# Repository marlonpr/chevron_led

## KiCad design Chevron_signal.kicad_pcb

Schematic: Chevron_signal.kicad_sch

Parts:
D1, D2, D3, D4, D5, D6, D7, D8, D9, D10, D11, D12, D13, D14, D15, D16, D17, D18, D19, D20, D21, D22, D23, D24, D25, D26, D27, D28, D29, D30, D31, D32, D33, D34, D35, D36, D37, D38, D39, D40, D41, D42, D43, D44, D45, D46, D47, D48, D49, D50, D51, D52, D53, D54, D55, D56, D57, D58, D59, D60, D61, D62, D63, D64, D65, D66, D67, D68, D69, D70, D71, D72, D73, D74, D75, D76, D77, D78, D79, D80, D81, D82, D83, D84, D85, D86, D87, D88, D89, D90, D91, D92, D93, D94, D95, D96, D97, D98, D99, D100, D101, D102, D103, D104, D105, D106, D107, D108, D109, D110, D111, D112, D113, D114, D115, D116, D117, D118, D119, D120, D121, D122, D123, D124, D125, D126, D127, D128, D129, D130, D131, D132, D133, D134, D135, D136, D137, D138, D139, D140, D141, D142, D143, D144: LED_CV28
P1: 282837-2; TE_282837-2; PARTREV G3
R1, R2, R3, R4, R5, R6, R7, R8, R9, R10, R11, R12, R13, R14, R15, R16, R17, R18, R19, R20, R21, R22, R23, R24, R25, R26, R27, R28, R29, R30, R31, R32, R33, R34, R35, R36, R37, R38, R39, R40, R41, R42, R43, R44, R45, R46, R47, R48, R49, R50, R51, R52, R53, R54, R55, R56, R57, R58, R59, R60, R61, R62, R63, R64, R65, R66, R67, R68, R69, R70, R71, R72, R73, R74, R75, R76, R77, R78, R79, R80, R81, R82, R83, R84, R85, R86, R87, R88, R89, R90, R91, R92, R93, R94, R95, R96, R97, R98, R99, R100, R101, R102, R103, R104, R105, R106, R107, R108, R109, R110, R111, R112, R113, R114, R115, R116, R117, R118, R119, R120: R_Small; R_Axial_DIN0207_L6.3mm_D2.5mm_P10.16mm_Horizontal

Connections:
+12V: P1.2, R1.2, R2.2, R3.2, R4.2, R5.2, R6.2, R7.2, R8.2, R9.2, R10.2, R11.2, R12.2, R13.2, R14.2, R15.2, R16.2, R17.2, R18.2, R19.2, R20.2, R21.2, R22.2, R23.2, R24.2, R25.2, R26.2, R27.2, R28.2, R29.2, R30.2, R31.2, R32.2, R33.2, R34.2, R35.2, R36.2, R37.2, R38.2, R39.2, R40.2, R41.2, R42.2, R43.2, R44.2, R45.2, R46.2, R47.2, R48.2, R49.2, R50.2, R51.2, R52.2, R53.2, R54.2, R55.2, R56.2, R57.2, R58.2, R59.2, R60.2, R61.2, R62.2, R63.2, R64.2, R65.2, R66.2, R67.2, R68.2, R69.2, R70.2, R71.2, R72.2, R73.2, R74.2, R75.2, R76.2, R77.2, R78.2, R79.2, R80.2, R81.2, R82.2, R83.2, R84.2, R85.2, R86.2, R87.2, R88.2, R89.2, R90.2, R91.2, R92.2, R93.2, R94.2, R95.2, R96.2, R97.2, R98.2, R99.2, R100.2, R101.2, R102.2, R103.2, R104.2, R105.2, R106.2, R107.2, R108.2, R109.2, R110.2, R111.2, R112.2, R113.2, R114.2, R115.2, R116.2, R117.2, R118.2, R119.2, R120.2
GND: D1.C1, D1.C2, D1.C3, D4.C3, D5.C1, D5.C2, D7.C3, D9.C1, D9.C2, D10.C3, D13.C1, D13.C2, D13.C3, D16.C3, D17.C1, D17.C2, D19.C3, D21.C1, D21.C2, D22.C3, D25.C1, D25.C2, D25.C3, D28.C3, D29.C1, D29.C2, D31.C3, D33.C1, D33.C2, D34.C3, D37.C1, D37.C2, D37.C3, D40.C3, D41.C1, D41.C2, D43.C3, D45.C1, D45.C2, D46.C3, D49.C1, D49.C2, D49.C3, D52.C3, D53.C1, D53.C2, D55.C3, D57.C1, D57.C2, D58.C3, D61.C1, D61.C2, D61.C3, D64.C3, D65.C1, D65.C2, D67.C3, D69.C1, D69.C2, D70.C3, D73.C1, D73.C2, D73.C3, D76.C3, D77.C1, D77.C2, D79.C3, D81.C1, D81.C2, D82.C3, D85.C1, D85.C2, D85.C3, D88.C3, D89.C1, D89.C2, D91.C3, D93.C1, D93.C2, D94.C3, D97.C1, D97.C2, D97.C3, D100.C3, D101.C1, D101.C2, D103.C3, D105.C1, D105.C2, D106.C3, D109.C1, D109.C2, D109.C3, D112.C3, D113.C1, D113.C2, D115.C3, D117.C1, D117.C2, D118.C3, D121.C1, D121.C2, D121.C3, D124.C3, D125.C1, D125.C2, D127.C3, D129.C1, D129.C2, D130.C3, D133.C1, D133.C2, D133.C3, D136.C3, D137.C1, D137.C2, D139.C3, D141.C1, D141.C2, D142.C3, P1.1
unnamed: D1.A1, D2.C1
unnamed: D1.A2, D2.C2
unnamed: D1.A3, D2.C3
unnamed: D2.A1, D3.C1
unnamed: D2.A2, D3.C2
unnamed: D2.A3, D3.C3
unnamed: D3.A1, D4.C1
unnamed: D3.A2, D4.C2
unnamed: D3.A3, R1.1
unnamed: D4.A1, R2.1
unnamed: D4.A2, R3.1
unnamed: D4.A3, D5.C3
unnamed: D5.A1, D6.C1
unnamed: D5.A2, D6.C2
unnamed: D5.A3, D6.C3
unnamed: D6.A1, D7.C1
unnamed: D6.A2, D7.C2
unnamed: D6.A3, R4.1
unnamed: D7.A1, D8.C1
unnamed: D7.A2, D8.C2
unnamed: D7.A3, D8.C3
unnamed: D8.A1, R5.1
unnamed: D8.A2, R6.1
unnamed: D8.A3, D9.C3
unnamed: D9.A3, R7.1
unnamed: D10.A1, D11.C1
unnamed: D10.A2, D11.C2
unnamed: D10.A3, D11.C3
unnamed: D9.A1, D10.C1
unnamed: D9.A2, D10.C2
unnamed: D11.A1, D12.C1
unnamed: D11.A2, D12.C2
unnamed: D11.A3, D12.C3
unnamed: D12.A1, R8.1
unnamed: D12.A2, R9.1
unnamed: D12.A3, R10.1
unnamed: D13.A1, D14.C1
unnamed: D13.A2, D14.C2
unnamed: D13.A3, D14.C3
unnamed: D14.A1, D15.C1
unnamed: D14.A2, D15.C2
unnamed: D14.A3, D15.C3
unnamed: D15.A1, D16.C1
unnamed: D15.A2, D16.C2
unnamed: D15.A3, R11.1
unnamed: D16.A1, R12.1
unnamed: D16.A2, R13.1
unnamed: D16.A3, D17.C3
unnamed: D17.A1, D18.C1
unnamed: D17.A2, D18.C2
unnamed: D17.A3, D18.C3
unnamed: D18.A1, D19.C1
unnamed: D18.A2, D19.C2
unnamed: D18.A3, R14.1
unnamed: D19.A1, D20.C1
unnamed: D19.A2, D20.C2
unnamed: D19.A3, D20.C3
unnamed: D20.A1, R15.1
unnamed: D20.A2, R16.1
unnamed: D20.A3, D21.C3
unnamed: D21.A1, D22.C1
unnamed: D21.A2, D22.C2
unnamed: D21.A3, R17.1
unnamed: D22.A1, D23.C1
unnamed: D22.A2, D23.C2
unnamed: D22.A3, D23.C3
unnamed: D23.A1, D24.C1
unnamed: D23.A2, D24.C2
unnamed: D23.A3, D24.C3
unnamed: D24.A1, R18.1
unnamed: D24.A2, R19.1
unnamed: D24.A3, R20.1
unnamed: D25.A1, D26.C1
unnamed: D25.A2, D26.C2
unnamed: D25.A3, D26.C3
unnamed: D26.A1, D27.C1
unnamed: D26.A2, D27.C2
unnamed: D26.A3, D27.C3
unnamed: D27.A1, D28.C1
unnamed: D27.A2, D28.C2
unnamed: D27.A3, R21.1
unnamed: D28.A1, R22.1
unnamed: D28.A2, R23.1
unnamed: D28.A3, D29.C3
unnamed: D29.A1, D30.C1
unnamed: D29.A2, D30.C2
unnamed: D29.A3, D30.C3
unnamed: D30.A1, D31.C1
unnamed: D30.A2, D31.C2
unnamed: D30.A3, R24.1
unnamed: D31.A1, D32.C1
unnamed: D31.A2, D32.C2
unnamed: D31.A3, D32.C3
unnamed: D32.A1, R25.1
unnamed: D32.A2, R26.1
unnamed: D32.A3, D33.C3
unnamed: D33.A1, D34.C1
unnamed: D33.A2, D34.C2
unnamed: D33.A3, R27.1
unnamed: D34.A1, D35.C1
unnamed: D34.A2, D35.C2
unnamed: D34.A3, D35.C3
unnamed: D35.A1, D36.C1
unnamed: D35.A2, D36.C2
unnamed: D35.A3, D36.C3
unnamed: D36.A1, R28.1
unnamed: D36.A2, R29.1
unnamed: D36.A3, R30.1
unnamed: D37.A1, D38.C1
unnamed: D37.A2, D38.C2
unnamed: D37.A3, D38.C3
unnamed: D38.A1, D39.C1
unnamed: D38.A2, D39.C2
unnamed: D38.A3, D39.C3
unnamed: D39.A1, D40.C1
unnamed: D39.A2, D40.C2
unnamed: D39.A3, R31.1
unnamed: D40.A1, R32.1
unnamed: D40.A2, R33.1
unnamed: D40.A3, D41.C3
unnamed: D41.A1, D42.C1
unnamed: D41.A2, D42.C2
unnamed: D41.A3, D42.C3
unnamed: D42.A1, D43.C1
unnamed: D42.A2, D43.C2
unnamed: D42.A3, R34.1
unnamed: D43.A1, D44.C1
unnamed: D43.A2, D44.C2
unnamed: D43.A3, D44.C3
unnamed: D44.A1, R35.1
unnamed: D44.A2, R36.1
unnamed: D44.A3, D45.C3
unnamed: D45.A1, D46.C1
unnamed: D45.A2, D46.C2
unnamed: D45.A3, R37.1
unnamed: D46.A1, D47.C1
unnamed: D46.A2, D47.C2
unnamed: D46.A3, D47.C3
unnamed: D47.A1, D48.C1
unnamed: D47.A2, D48.C2
unnamed: D47.A3, D48.C3
unnamed: D48.A1, R38.1
unnamed: D48.A2, R39.1
unnamed: D48.A3, R40.1
unnamed: D49.A1, D50.C1
unnamed: D49.A2, D50.C2
unnamed: D49.A3, D50.C3
unnamed: D50.A1, D51.C1
unnamed: D50.A2, D51.C2
unnamed: D50.A3, D51.C3
unnamed: D51.A1, D52.C1
unnamed: D51.A2, D52.C2
unnamed: D51.A3, R41.1
unnamed: D52.A1, R42.1
unnamed: D52.A2, R43.1
unnamed: D52.A3, D53.C3
unnamed: D53.A1, D54.C1
unnamed: D53.A2, D54.C2
unnamed: D53.A3, D54.C3
unnamed: D54.A1, D55.C1
unnamed: D54.A2, D55.C2
unnamed: D54.A3, R44.1
unnamed: D55.A1, D56.C1
unnamed: D55.A2, D56.C2
unnamed: D55.A3, D56.C3
unnamed: D56.A1, R45.1
unnamed: D56.A2, R46.1
unnamed: D56.A3, D57.C3
unnamed: D57.A1, D58.C1
unnamed: D57.A2, D58.C2
unnamed: D57.A3, R47.1
unnamed: D58.A1, D59.C1
unnamed: D58.A2, D59.C2
unnamed: D58.A3, D59.C3
unnamed: D59.A1, D60.C1
unnamed: D59.A2, D60.C2
unnamed: D59.A3, D60.C3
unnamed: D60.A1, R48.1
unnamed: D60.A2, R49.1
unnamed: D60.A3, R50.1
unnamed: D61.A1, D62.C1
unnamed: D61.A2, D62.C2
unnamed: D61.A3, D62.C3
unnamed: D62.A1, D63.C1
unnamed: D62.A2, D63.C2
unnamed: D62.A3, D63.C3
unnamed: D63.A1, D64.C1
unnamed: D63.A2, D64.C2
unnamed: D63.A3, R51.1
unnamed: D64.A1, R52.1
unnamed: D64.A2, R53.1
unnamed: D64.A3, D65.C3
unnamed: D65.A1, D66.C1
unnamed: D65.A2, D66.C2
unnamed: D65.A3, D66.C3
unnamed: D66.A1, D67.C1
unnamed: D66.A2, D67.C2
unnamed: D66.A3, R54.1
unnamed: D67.A1, D68.C1
unnamed: D67.A2, D68.C2
unnamed: D67.A3, D68.C3
unnamed: D68.A1, R55.1
unnamed: D68.A2, R56.1
unnamed: D68.A3, D69.C3
unnamed: D69.A1, D70.C1
unnamed: D69.A2, D70.C2
unnamed: D69.A3, R57.1
unnamed: D70.A1, D71.C1
unnamed: D70.A2, D71.C2
unnamed: D70.A3, D71.C3
unnamed: D71.A1, D72.C1
unnamed: D71.A2, D72.C2
unnamed: D71.A3, D72.C3
unnamed: D72.A1, R58.1
unnamed: D72.A2, R59.1
unnamed: D72.A3, R60.1
unnamed: D73.A1, D74.C1
unnamed: D73.A2, D74.C2
unnamed: D73.A3, D74.C3
unnamed: D74.A1, D75.C1
unnamed: D74.A2, D75.C2
unnamed: D74.A3, D75.C3
unnamed: D75.A1, D76.C1
unnamed: D75.A2, D76.C2
unnamed: D75.A3, R61.1
unnamed: D76.A1, R62.1
unnamed: D76.A2, R63.1
unnamed: D76.A3, D77.C3
unnamed: D77.A1, D78.C1
unnamed: D77.A2, D78.C2
unnamed: D77.A3, D78.C3
unnamed: D78.A1, D79.C1
unnamed: D78.A2, D79.C2
unnamed: D78.A3, R64.1
unnamed: D79.A1, D80.C1
unnamed: D79.A2, D80.C2
unnamed: D79.A3, D80.C3
unnamed: D80.A1, R65.1
unnamed: D80.A2, R66.1
unnamed: D80.A3, D81.C3
unnamed: D81.A1, D82.C1
unnamed: D81.A2, D82.C2
unnamed: D81.A3, R67.1
unnamed: D82.A1, D83.C1
unnamed: D82.A2, D83.C2
unnamed: D82.A3, D83.C3
unnamed: D83.A1, D84.C1
unnamed: D83.A2, D84.C2
unnamed: D83.A3, D84.C3
unnamed: D84.A1, R68.1
unnamed: D84.A2, R69.1
unnamed: D84.A3, R70.1
unnamed: D85.A1, D86.C1
unnamed: D85.A2, D86.C2
unnamed: D85.A3, D86.C3
unnamed: D86.A1, D87.C1
unnamed: D86.A2, D87.C2
unnamed: D86.A3, D87.C3
unnamed: D87.A1, D88.C1
unnamed: D87.A2, D88.C2
unnamed: D87.A3, R71.1
unnamed: D88.A1, R72.1
unnamed: D88.A2, R73.1
unnamed: D88.A3, D89.C3
unnamed: D89.A1, D90.C1
unnamed: D89.A2, D90.C2
unnamed: D89.A3, D90.C3
unnamed: D90.A1, D91.C1
unnamed: D90.A2, D91.C2
unnamed: D90.A3, R74.1
unnamed: D91.A1, D92.C1
unnamed: D91.A2, D92.C2
unnamed: D91.A3, D92.C3
unnamed: D92.A1, R75.1
unnamed: D92.A2, R76.1
unnamed: D92.A3, D93.C3
unnamed: D93.A1, D94.C1
unnamed: D93.A2, D94.C2
unnamed: D93.A3, R77.1
unnamed: D94.A1, D95.C1
unnamed: D94.A2, D95.C2
unnamed: D94.A3, D95.C3
unnamed: D95.A1, D96.C1
unnamed: D95.A2, D96.C2
unnamed: D95.A3, D96.C3
unnamed: D96.A1, R78.1
unnamed: D96.A2, R79.1
unnamed: D96.A3, R80.1
unnamed: D97.A1, D98.C1
unnamed: D97.A2, D98.C2
unnamed: D97.A3, D98.C3
unnamed: D98.A1, D99.C1
unnamed: D98.A2, D99.C2
unnamed: D98.A3, D99.C3
unnamed: D99.A3, R81.1
unnamed: D100.A1, R82.1
unnamed: D100.A2, R83.1
unnamed: D100.A3, D101.C3
unnamed: D99.A1, D100.C1
unnamed: D99.A2, D100.C2
unnamed: D101.A1, D102.C1
unnamed: D101.A2, D102.C2
unnamed: D101.A3, D102.C3
unnamed: D102.A1, D103.C1
unnamed: D102.A2, D103.C2
unnamed: D102.A3, R84.1
unnamed: D103.A1, D104.C1
unnamed: D103.A2, D104.C2
unnamed: D103.A3, D104.C3
unnamed: D104.A1, R85.1
unnamed: D104.A2, R86.1
unnamed: D104.A3, D105.C3
unnamed: D105.A1, D106.C1
unnamed: D105.A2, D106.C2
unnamed: D105.A3, R87.1
unnamed: D106.A1, D107.C1
unnamed: D106.A2, D107.C2
unnamed: D106.A3, D107.C3
unnamed: D107.A1, D108.C1
unnamed: D107.A2, D108.C2
unnamed: D107.A3, D108.C3
unnamed: D108.A1, R88.1
unnamed: D108.A2, R89.1
unnamed: D108.A3, R90.1
unnamed: D109.A1, D110.C1
unnamed: D109.A2, D110.C2
unnamed: D109.A3, D110.C3
unnamed: D110.A1, D111.C1
unnamed: D110.A2, D111.C2
unnamed: D110.A3, D111.C3
unnamed: D111.A1, D112.C1
unnamed: D111.A2, D112.C2
unnamed: D111.A3, R91.1
unnamed: D112.A1, R92.1
unnamed: D112.A2, R93.1
unnamed: D112.A3, D113.C3
unnamed: D113.A1, D114.C1
unnamed: D113.A2, D114.C2
unnamed: D113.A3, D114.C3
unnamed: D114.A1, D115.C1
unnamed: D114.A2, D115.C2
unnamed: D114.A3, R94.1
unnamed: D115.A1, D116.C1
unnamed: D115.A2, D116.C2
unnamed: D115.A3, D116.C3
unnamed: D116.A1, R95.1
unnamed: D116.A2, R96.1
unnamed: D116.A3, D117.C3
unnamed: D117.A1, D118.C1
unnamed: D117.A2, D118.C2
unnamed: D117.A3, R97.1
unnamed: D118.A1, D119.C1
unnamed: D118.A2, D119.C2
unnamed: D118.A3, D119.C3
unnamed: D119.A1, D120.C1
unnamed: D119.A2, D120.C2
unnamed: D119.A3, D120.C3
unnamed: D120.A1, R98.1
unnamed: D120.A2, R99.1
unnamed: D120.A3, R100.1
unnamed: D121.A1, D122.C1
unnamed: D121.A2, D122.C2
unnamed: D121.A3, D122.C3
unnamed: D122.A1, D123.C1
unnamed: D122.A2, D123.C2
unnamed: D122.A3, D123.C3
unnamed: D123.A1, D124.C1
unnamed: D123.A2, D124.C2
unnamed: D123.A3, R101.1
unnamed: D124.A1, R102.1
unnamed: D124.A2, R103.1
unnamed: D124.A3, D125.C3
unnamed: D125.A1, D126.C1
unnamed: D125.A2, D126.C2
unnamed: D125.A3, D126.C3
unnamed: D126.A1, D127.C1
unnamed: D126.A2, D127.C2
unnamed: D126.A3, R104.1
unnamed: D127.A1, D128.C1
unnamed: D127.A2, D128.C2
unnamed: D127.A3, D128.C3
unnamed: D128.A1, R105.1
unnamed: D128.A2, R106.1
unnamed: D128.A3, D129.C3
unnamed: D129.A1, D130.C1
unnamed: D129.A2, D130.C2
unnamed: D129.A3, R107.1
unnamed: D130.A1, D131.C1
unnamed: D130.A2, D131.C2
unnamed: D130.A3, D131.C3
unnamed: D131.A1, D132.C1
unnamed: D131.A2, D132.C2
unnamed: D131.A3, D132.C3
unnamed: D132.A1, R108.1
unnamed: D132.A2, R109.1
unnamed: D132.A3, R110.1
unnamed: D133.A1, D134.C1
unnamed: D133.A2, D134.C2
unnamed: D133.A3, D134.C3
unnamed: D134.A1, D135.C1
unnamed: D134.A2, D135.C2
unnamed: D134.A3, D135.C3
unnamed: D135.A1, D136.C1
unnamed: D135.A2, D136.C2
unnamed: D135.A3, R111.1
unnamed: D136.A1, R112.1
unnamed: D136.A2, R113.1
unnamed: D136.A3, D137.C3
unnamed: D137.A1, D138.C1
unnamed: D137.A2, D138.C2
unnamed: D137.A3, D138.C3
unnamed: D138.A1, D139.C1
unnamed: D138.A2, D139.C2
unnamed: D138.A3, R114.1
unnamed: D139.A1, D140.C1
unnamed: D139.A2, D140.C2
unnamed: D139.A3, D140.C3
unnamed: D140.A1, R115.1
unnamed: D140.A2, R116.1
unnamed: D140.A3, D141.C3
unnamed: D141.A1, D142.C1
unnamed: D141.A2, D142.C2
unnamed: D141.A3, R117.1
unnamed: D142.A1, D143.C1
unnamed: D142.A2, D143.C2
unnamed: D142.A3, D143.C3
unnamed: D143.A1, D144.C1
unnamed: D143.A2, D144.C2
unnamed: D143.A3, D144.C3
unnamed: D144.A1, R118.1
unnamed: D144.A2, R119.1
unnamed: D144.A3, R120.1

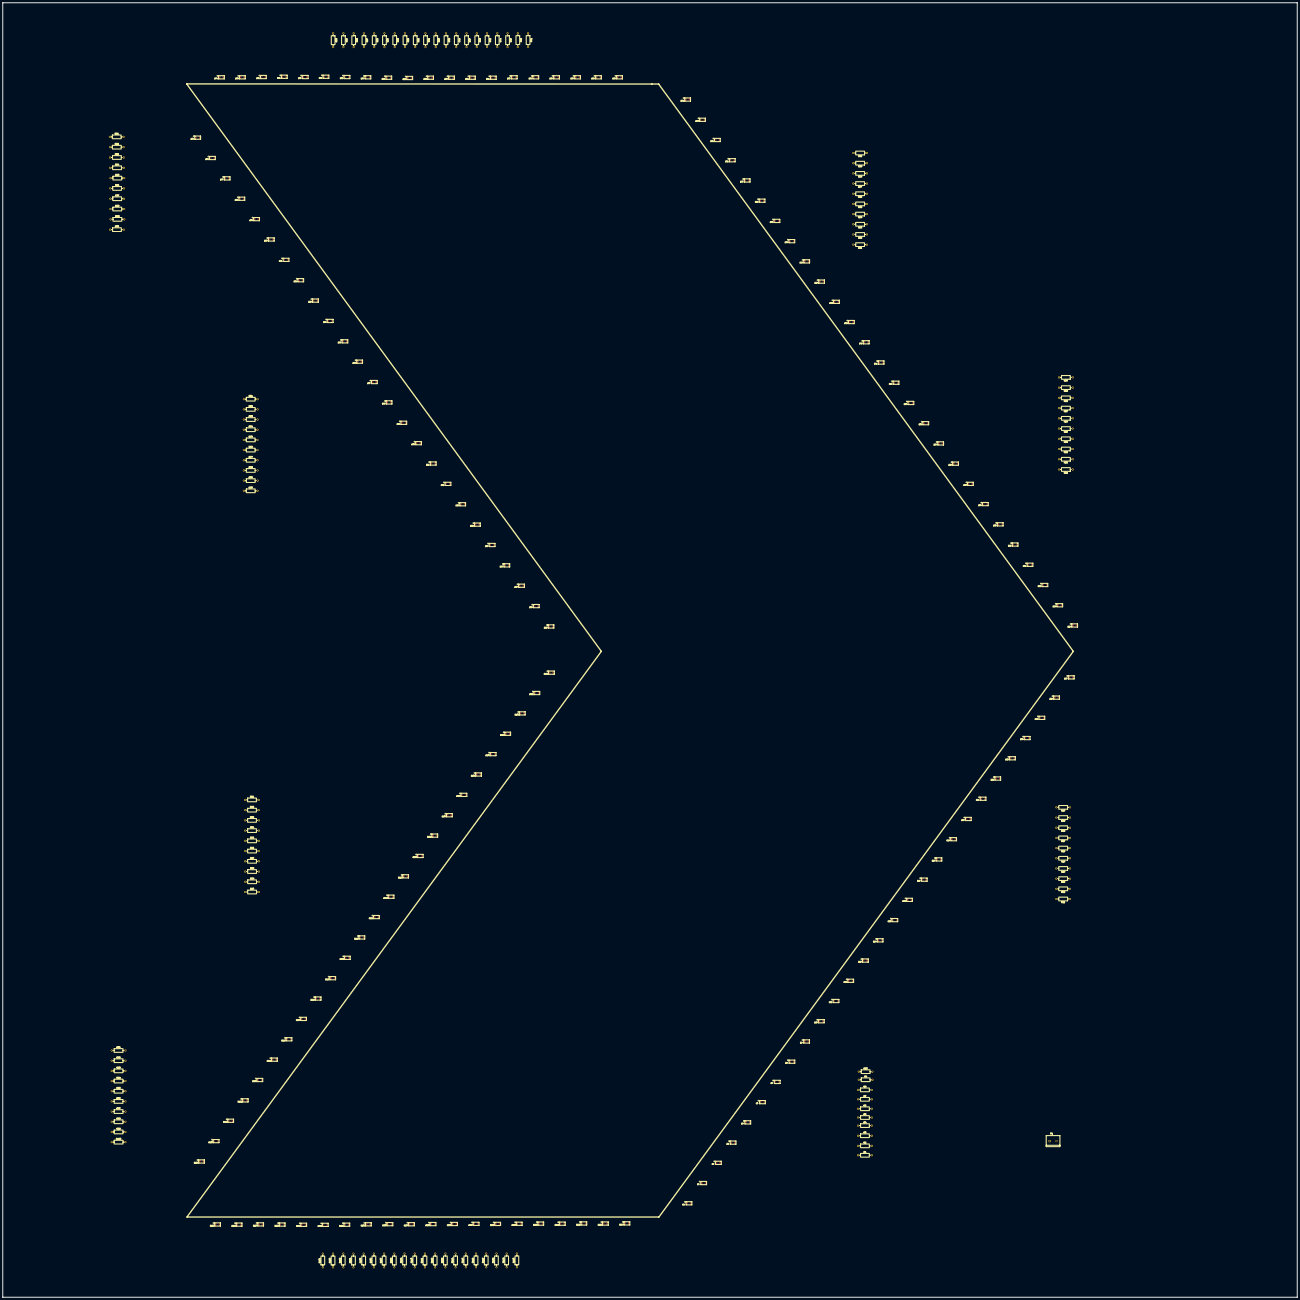
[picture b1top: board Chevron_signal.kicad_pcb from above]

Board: 2 copper layers, 960.0 x 960.0 mm, 265 parts (0 on the bottom side), 434 nets, no tracks yet.

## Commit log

2025-09-04 cv28 v1.0
2025-09-09 cv28 v1.1
2025-09-09 cv28 v1.2
2025-09-10 cv28 v1.3
